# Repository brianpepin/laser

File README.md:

# The Laser Project
This repository contains a design for a diode pumped solid state laser that emits a green 532nm beam.  The unit is battery operated and rechargable with a runtime of approximately 30 minutes.

## Versions
Version 2.1 of the hardware and software is now live. Here is a summary of the changes:
1. The control board now uses a more modern MCU. Display refreshes are 8x faster and I was able to remove a number of components from the board due to the enhanced peripheral support on the new MCU.
2. Encoders are now velocity sensitive.
3. Calibration for the output power monitor now can be done through the UI.
4. The laser design has changed and the maximum output power is now 3x what it was in version 1.

## Repository Organization

The repository contains the following directories.

### Hardware
The Hardware directory contains KiCad files for schematics and board designs for the electronics.  There are three boards in total:

1. The **Power** board is the main power supply. It contains a battery charger, power control, power monitoring, fan controller, and two 50A constant current power supplies.

2. The **TEC** board contains four independent channels for controlling thermo-electric coolers. Each channel can control up to 20A of cooling using direct battery voltage.

3. The **Control** board is a small MCU and display for running the laser.  The board is based on the aging ATMEGA328p....but it would be easy to swap this to a newer MCU.

**Update:** Version 2.1 of the hardware now uses AVR128DB64 as it's MCU. This MCU has a lot more memory, a much faster speed, and perhipherial updates (like controllable schmitt triggers on inputs) that greatly simplified the rest of the board.

The power and TEC boards must both be bonded to heat sinks on the underside of the board using a non-conductive thermal layer. Boards use Deans connectors for high power and these connectors were modified (pins trimmed) so when soldered the back of the board remains relatively flat.

The system is designed to run off a 2S LiPo pack (I'm using two 8Ah packs in parallel). If you need higher voltage for the TECs you can go to 3S but may need to modify the charging circuit, which is designed for a 2S cell.

### Software
The software directory contains the source code for the controller. It uses Platform.IO in Visual Studio Code and levages Arduino libraries for convenience, especially for driving the display. Installing Platform.IO should be sufficient to find dependent libraries.
The software is organized to have a lib directory that contains generic driver code for chips used on each of the boards.  In the src directory these generic classes are wrapped by higher level classes that abstract their use.  For example, lib has directories called ADC104S021 and DAC108S085 for controlling ADC and DAC chips, and src has a class called TEC that uses both these lower level classes but provides an interface in degrees C.

### Optics
Optics contains files relevant to the optical layout.  Files ending in .rez are Rezonator files, which is an open-source program available at http://www.rezonator.orion-project.org which can do ABCD matrix analysis of laser cavities for stability and Gaussian beam analysis.

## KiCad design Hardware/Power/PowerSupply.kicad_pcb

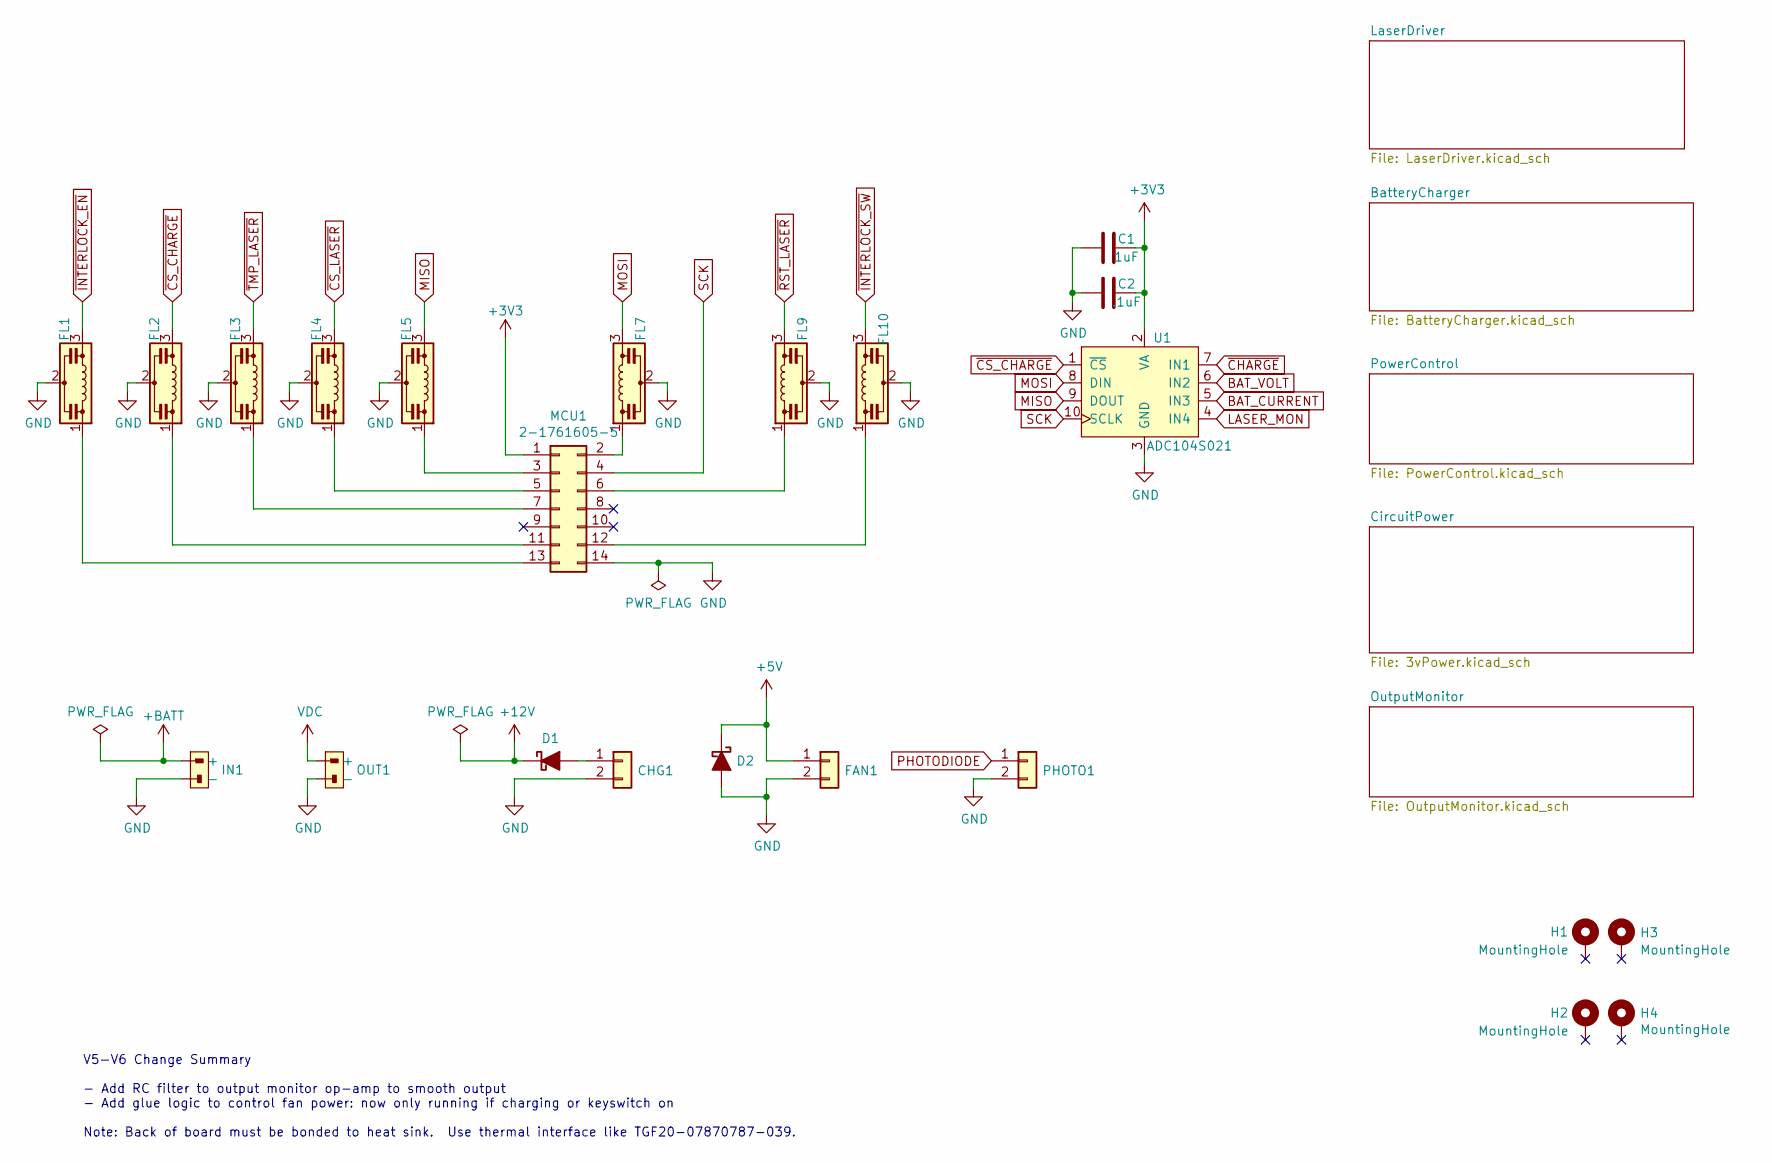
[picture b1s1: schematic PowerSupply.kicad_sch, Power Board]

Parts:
C1: 1uF; C_0805_2012Metric; PartNo UMF212B7105KGHT
C2: .1uF; C_0805_2012Metric; PartNo C0805X104M5RACTU
CHG1: 105313-1102; Molex_Nano-Fit_105313-xx02_1x02_P2.50mm_Horizontal; PartNo 105313-1102
D1: CDBA540-HF; D_SMA; PartNo CDBA540-HF
D2: V1FM15-M3/H; D_SOD-123F; PartNo V1FM15-M3/H
FAN1: 53398-0267; 533980267; PartNo 53398-0267
FL1, FL2, FL3, FL4, FL5, FL7, FL9, FL10: NFL21SP206X1C7D; EMI_805; PartNo NFL21SP206X1C7D
H1, H2, H3, H4: MountingHole; MountingHole_3.2mm_M3_Pad_Via
IN1: DEANS; Connector_Deans_Male
MCU1: 2-1761605-5; IDC-Header_2x07_P2.54mm_Horizontal; PartNo 2-1761605-5
OUT1: DEANS; Connector_Deans_Female
PHOTO1: 53398-0267; 533980267; PartNo 53398-0267
U1: ADC104S021; VSSOP-10_3x3mm_P0.5mm; PartNo ADC104S021CIMMX/NOPB

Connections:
+3V3: C1.1, C2.1, MCU1.1, U1.2 (VA); also elsewhere on the board
+5V: D2.1 (K), FAN1.1; also elsewhere on the board
+12V: D1.1 (K); also elsewhere on the board
+BATT: IN1.+; also elsewhere on the board
BAT_CURRENT: U1.5 (IN3); also elsewhere on the board
BAT_VOLT: U1.6 (IN2); also elsewhere on the board
GND: C1.2, C2.2, CHG1.2, D2.2 (A), FAN1.2, FL1.2, FL2.2, FL3.2, FL4.2, FL5.2, FL7.2, FL9.2, FL10.2, IN1.-, MCU1.14, OUT1.-, PHOTO1.2, U1.3 (GND); also elsewhere on the board
LASER_MON: U1.4 (IN4); also elsewhere on the board
MISO: FL5.3, U1.9 (DOUT); also elsewhere on the board
MOSI: FL7.3, U1.8 (DIN); also elsewhere on the board
unnamed: CHG1.1, D1.2 (A)
unnamed: FL7.1, MCU1.2
unnamed: FL5.1, MCU1.3
unnamed: FL4.1, MCU1.5
unnamed: FL9.1, MCU1.6
unnamed: FL3.1, MCU1.7
unnamed: FL2.1, MCU1.11
unnamed: FL10.1, MCU1.12
unnamed: FL1.1, MCU1.13
PHOTODIODE: PHOTO1.1; also elsewhere on the board
SCK: MCU1.4, U1.10 (SCLK); also elsewhere on the board
VDC: OUT1.+; also elsewhere on the board
~CHARGE: U1.7 (IN1); also elsewhere on the board
~CS_CHARGE: FL2.3, U1.1 (~CS)
~CS_LASER: FL4.3; also elsewhere on the board
~INTERLOCK_EN: FL1.3; also elsewhere on the board
~INTERLOCK_SW: FL10.3; also elsewhere on the board
~RST_LASER: FL9.3; also elsewhere on the board
~TMP_LASER: FL3.3; also elsewhere on the board

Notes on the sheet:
V5-V6 Change Summary - Add RC filter to output monitor op-amp to smooth output - Add glue logic to control fan power: now only running if charging or keyswitch on Note: Back of board must be bonded to heat sink. Use thermal interface like TGF20-07870787-039.

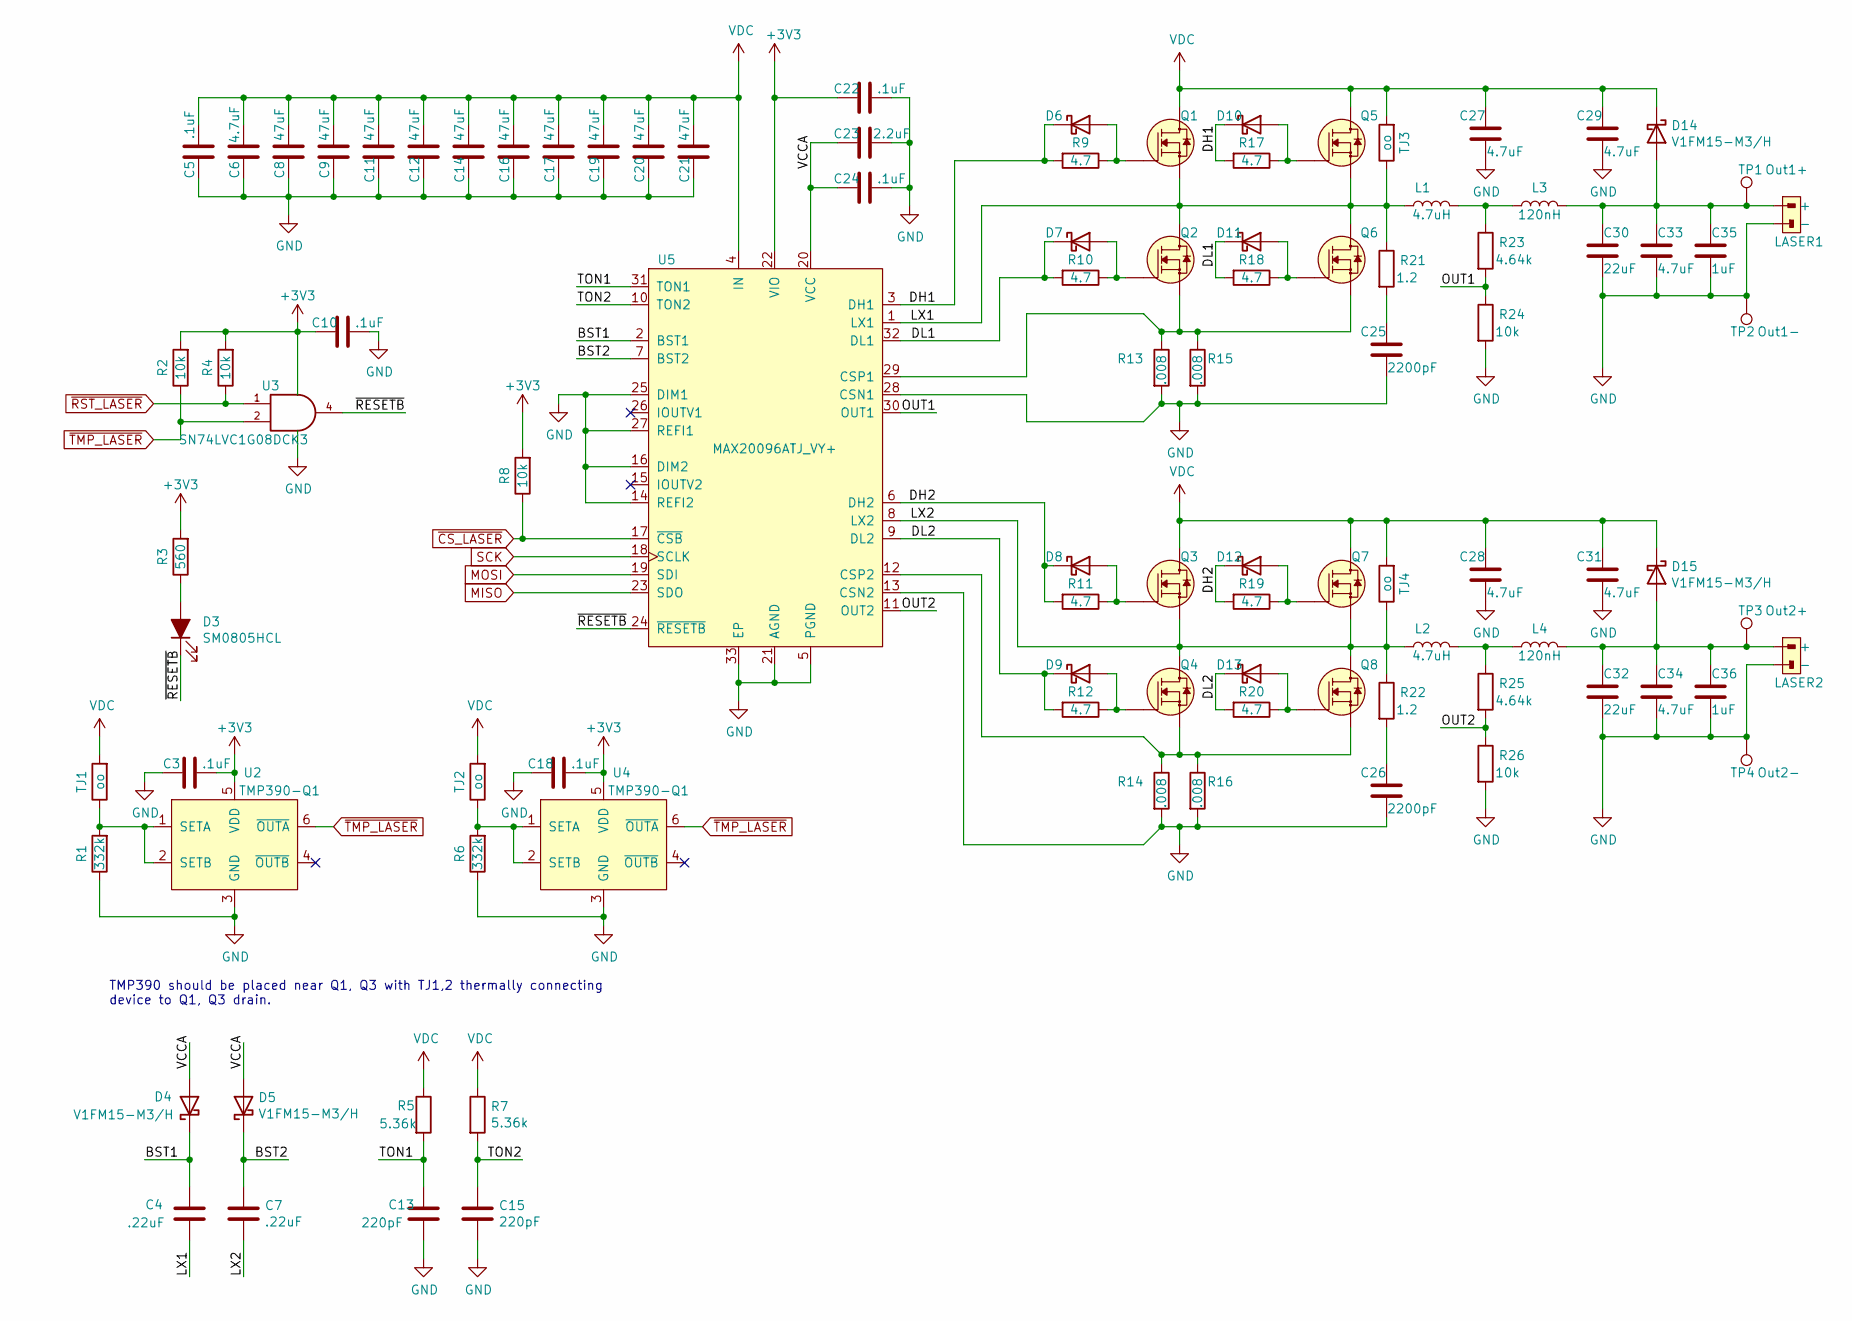
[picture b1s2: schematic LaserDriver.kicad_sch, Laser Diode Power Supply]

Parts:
C3, C5, C10, C18, C22, C24: .1uF; C_0805_2012Metric; PartNo C0805X104M5RACTU
C4, C7: .22uF; C_0805_2012Metric; PartNo GRM21AR72A224KAC5K
C6, C27, C28, C29, C31, C33, C34: 4.7uF; C_0805_2012Metric; PartNo JMK212B7475KGHT
C8, C9, C11, C12, C14, C16, C17, C19, C20, C21: 47uF; C_1206_3216Metric; PartNo C3216JB1E476M160AC
C13, C15: 220pF; C_0805_2012Metric; PartNo C0805C221K1HACTU
C23: 2.2uF; C_0805_2012Metric; PartNo GCM21BR71E225KA73L
C25, C26: 2200pF; C_0805_2012Metric; PartNo C0805C222K3GECTU
C30, C32: 22uF; C_1206_3216Metric; PartNo C3216X5R1V226M160AC
C35, C36: 1uF; C_0805_2012Metric; PartNo UMF212B7105KGHT
D3: SM0805HCL; LED_0805_2012Metric; PartNo SM0805HCL
D4, D5, D6, D7, D8, D9, D10, D11, D12, D13, D14, D15: V1FM15-M3/H; D_SOD-123F; PartNo V1FM15-M3/H
L1, L2: 4.7uH; Inductor_Kemet_MPX1D2213; PartNo MPXV1D2213L4R7
L3, L4: 120nH; Inductor_TDK_VLBS1007083; PartNo VLBU1007090T-R12L
LASER1, LASER2: DEANS; Connector_Deans_Female
Q1, Q2, Q3, Q4, Q5, Q6, Q7, Q8: PSMN1R5-25MLHX; LFPAK33; PartNo PSMN1R5-25MLHX
R1, R6: 332k; R_0805_2012Metric; PartNo RT0805FRE07332KL
R2, R4, R8, R24, R26: 10k; R_0805_2012Metric; PartNo ERJ-6ENF1002V
R3: 560; R_0805_2012Metric; PartNo ERJ-6ENF5600V
R5, R7: 5.36k; R_0805_2012Metric; PartNo ERJ-6ENF5361V
R9, R10, R11, R12, R17, R18, R19, R20: 4.7; R_0805_2012Metric; PartNo ERJ-P06J4R7V
R13, R14, R15, R16: .008; R_2818_7158Metric_Kelvin; PartNo WSHM28188L000FEA
R21, R22: 1.2; R_0805_2012Metric; PartNo ERJ-6BQF1R2V
R23, R25: 4.64k; R_0805_2012Metric; PartNo ERJ-6ENF4641V
TJ1, TJ2, TJ3, TJ4: oo; R_1206_3216Metric; PartNo THJP1206AST1
TP1: Out1+; TestPoint_THTPad_1.0x1.0mm_Drill0.5mm
TP2: Out1-; TestPoint_THTPad_1.0x1.0mm_Drill0.5mm
TP3: Out2+; TestPoint_THTPad_1.0x1.0mm_Drill0.5mm
TP4: Out2-; TestPoint_THTPad_1.0x1.0mm_Drill0.5mm
U2, U4: TMP390-Q1; SOT-563; PartNo TMP390AQDRLRQ1
U3: SN74LVC1G08DCK3; SC-70-5; PartNo SN74LVC1G08DCK3
U5: MAX20096ATJ_VY+; QFN-32-1EP_5x5mm_P0.5mm_EP3.1x3.1mm_ThermalVias; PartNo MAX20096ATJ/VY+

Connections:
+3V3: C3.1, C10.2, C18.1, C22.2, R2.2, R3.2, R4.2, R8.2, U2.5 (VDD), U3.5 (VCC), U4.5 (VDD), U5.22 (VIO); also elsewhere on the board
/LaserDriver/BST1: C4.1, D4.1 (K), U5.2 (BST1)
/LaserDriver/BST2: C7.1, D5.1 (K), U5.7 (BST2)
/LaserDriver/DH1: D6.1 (K), D10.1 (K), R9.2, R17.2, U5.3 (DH1)
/LaserDriver/DH2: D8.1 (K), D12.1 (K), R11.2, R19.2, U5.6 (DH2)
/LaserDriver/DL1: D7.1 (K), D11.1 (K), R10.2, R18.2, U5.32 (DL1)
/LaserDriver/DL2: D9.1 (K), D13.1 (K), R12.2, R20.2, U5.9 (DL2)
/LaserDriver/LX1: C4.2, L1.1, Q1.1 (S), Q1.2 (S), Q1.3 (S), Q2.5 (D), Q5.1 (S), Q5.2 (S), Q5.3 (S), Q6.5 (D), R21.1, TJ3.1, U5.1 (LX1)
/LaserDriver/LX2: C7.2, L2.1, Q3.1 (S), Q3.2 (S), Q3.3 (S), Q4.5 (D), Q7.1 (S), Q7.2 (S), Q7.3 (S), Q8.5 (D), R22.1, TJ4.1, U5.8 (LX2)
/LaserDriver/OUT1: R23.2, R24.1, U5.30 (OUT1)
/LaserDriver/OUT2: R25.2, R26.1, U5.11 (OUT2)
/LaserDriver/TON1: C13.1, R5.2, U5.31 (TON1)
/LaserDriver/TON2: C15.1, R7.2, U5.10 (TON2)
/LaserDriver/VCCA: C23.2, C24.2, D4.2 (A), D5.2 (A), U5.20 (VCC)
/LaserDriver/~RESETB: D3.1 (K), U3.4, U5.24 (~RESETB)
GND: C3.2, C5.2, C6.2, C8.2, C9.2, C10.1, C11.2, C12.2, C13.2, C14.2, C15.2, C16.2, C17.2, C18.2, C19.2, C20.2, C21.2, C22.1, C23.1, C24.1, C25.2, C26.2, C27.2, C28.2, C29.2, C30.2, C31.2, C32.2, C33.2, C34.2, C35.2, C36.2, LASER1.-, LASER2.-, R1.1, R6.1, R13.2, R14.2, R15.2, R16.2, R24.2, R26.2, TP2.1, TP4.1, U2.3 (GND), U3.3 (GND), U4.3 (GND), U5.5 (PGND), U5.13 (CSN2), U5.14 (REFI2), U5.16 (DIM2), U5.21 (AGND), U5.25 (DIM1), U5.27 (REFI1), U5.28 (CSN1), U5.33 (EP); also elsewhere on the board
MISO: U5.23 (SDO); also elsewhere on the board
MOSI: U5.19 (SDI); also elsewhere on the board
unnamed: C25.1, R21.2
unnamed: C26.1, R22.2
unnamed: D3.2 (A), R3.1
unnamed: D6.2 (A), Q1.4 (G), R9.1
unnamed: D7.2 (A), Q2.4 (G), R10.1
unnamed: D8.2 (A), Q3.4 (G), R11.1
unnamed: D9.2 (A), Q4.4 (G), R12.1
unnamed: D10.2 (A), Q5.4 (G), R17.1
unnamed: D11.2 (A), Q6.4 (G), R18.1
unnamed: D12.2 (A), Q7.4 (G), R19.1
unnamed: D13.2 (A), Q8.4 (G), R20.1
unnamed: C30.1, C33.1, C35.1, D14.2 (A), L3.2, LASER1.+, TP1.1
unnamed: C32.1, C34.1, C36.1, D15.2 (A), L4.2, LASER2.+, TP3.1
unnamed: L1.2, L3.1, R23.1
unnamed: L2.2, L4.1, R25.1
unnamed: R1.2, TJ1.1, U2.1 (SETA), U2.2 (SETB)
unnamed: R6.2, TJ2.1, U4.1 (SETA), U4.2 (SETB)
unnamed: Q2.1 (S), Q2.2 (S), Q2.3 (S), Q6.1 (S), Q6.2 (S), Q6.3 (S), R13.1, R15.1, U5.29 (CSP1)
unnamed: Q4.1 (S), Q4.2 (S), Q4.3 (S), Q8.1 (S), Q8.2 (S), Q8.3 (S), R14.1, R16.1, U5.12 (CSP2)
SCK: U5.18 (SCLK); also elsewhere on the board
VDC: C5.1, C6.1, C8.1, C9.1, C11.1, C12.1, C14.1, C16.1, C17.1, C19.1, C20.1, C21.1, C27.1, C28.1, C29.1, C31.1, D14.1 (K), D15.1 (K), Q1.5 (D), Q3.5 (D), Q5.5 (D), Q7.5 (D), R5.1, R7.1, TJ1.2, TJ2.2, TJ3.2, TJ4.2, U5.4 (IN); also elsewhere on the board
~CS_LASER: R8.1, U5.17 (~CSB); also elsewhere on the board
~RST_LASER: R4.1, U3.1; also elsewhere on the board
~TMP_LASER: R2.1, U2.6 (~OUTA), U3.2, U4.6 (~OUTA); also elsewhere on the board

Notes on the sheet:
TMP390 should be placed near Q1, Q3 with TJ1,2 thermally connecting device to Q1, Q3 drain.

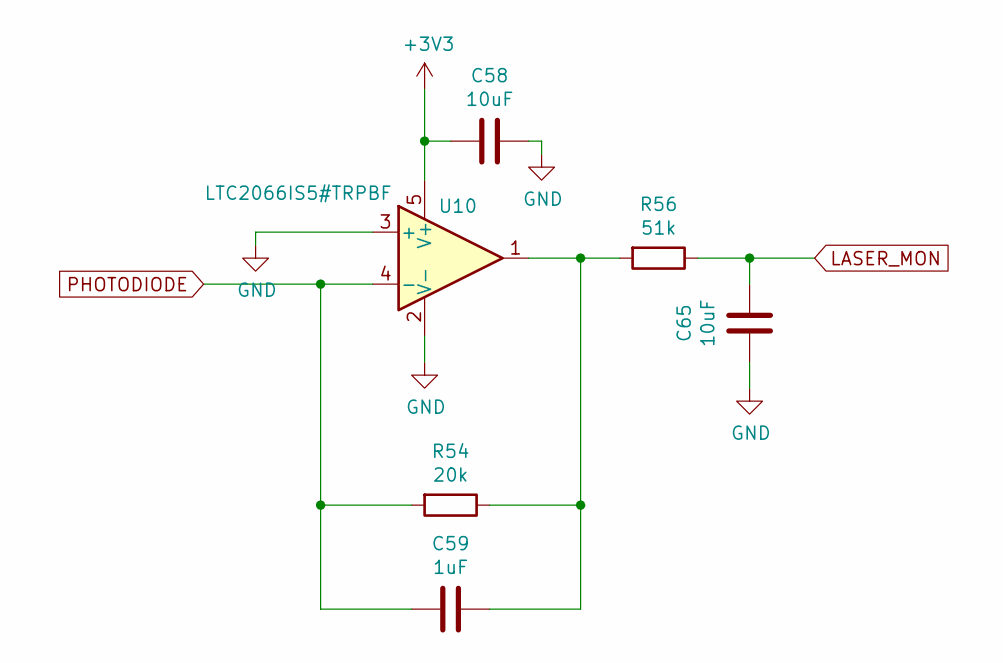
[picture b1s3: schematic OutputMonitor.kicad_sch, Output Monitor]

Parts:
C58, C65: 10uF; C_0805_2012Metric; PartNo C0805X104M5RACTU
C59: 1uF; C_0805_2012Metric; PartNo UMF212B7105KGHT
R54: 20k; R_0805_2012Metric; PartNo ERJ-P06D60R4V
R56: 51k; R_0805_2012Metric; PartNo ERJ-P06D60R4V
U10: LTC2066IS5#TRPBF; SOT-23-5; PartNo LTC2066IS5#TRPBF

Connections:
+3V3: C58.2, U10.5 (V+); also elsewhere on the board
GND: C58.1, C65.2, U10.2 (V-), U10.3 (+); also elsewhere on the board
LASER_MON: C65.1, R56.1; also elsewhere on the board
unnamed: C59.1, R54.1, R56.2, U10.1
PHOTODIODE: C59.2, R54.2, U10.4 (-); also elsewhere on the board

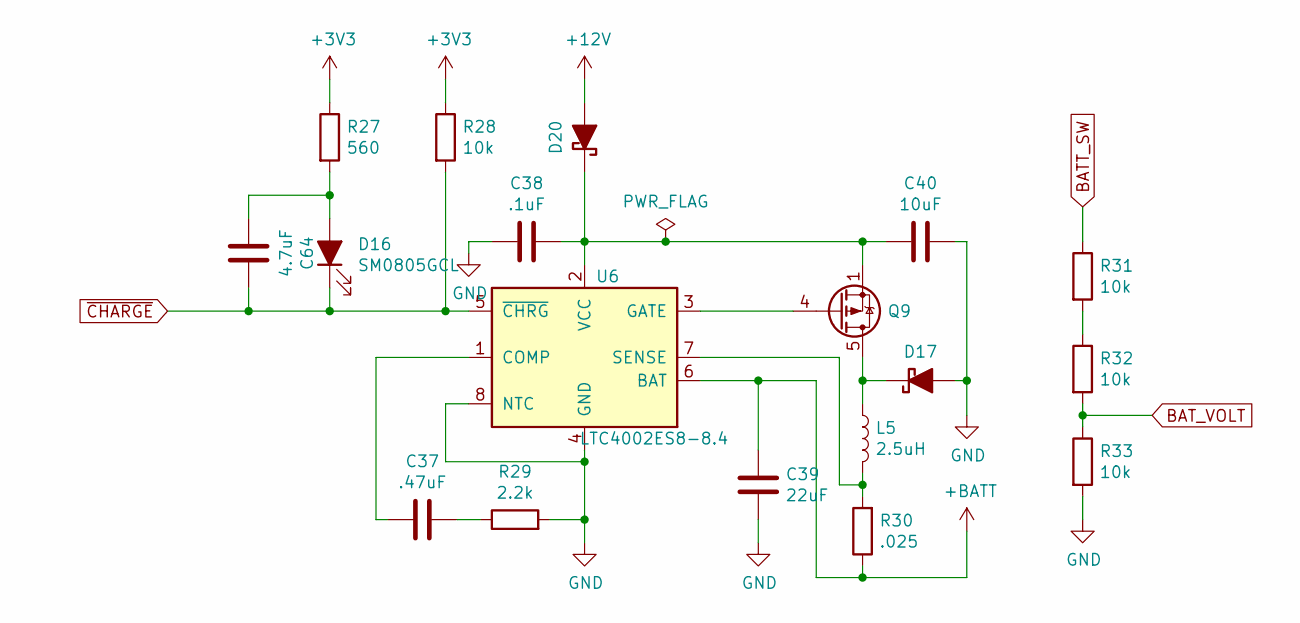
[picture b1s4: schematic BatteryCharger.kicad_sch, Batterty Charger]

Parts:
C37: .47uF; C_0805_2012Metric; PartNo C2012X7R1E474K125AA
C38: .1uF; C_0805_2012Metric; PartNo C0805X104M5RACTU
C39: 22uF; C_1206_3216Metric; PartNo C3216X5R1V226M160AC
C40: 10uF; C_1206_3216Metric; PartNo GMK316AB7106KL-TR
C64: 4.7uF; C_0805_2012Metric; PartNo JMK212B7475KGHT
D16: SM0805GCL; LED_0805_2012Metric; PartNo SM0805GCL
D17, D20: CDBA540-HF; D_SMA; PartNo CDBA540-HF
L5: 2.5uH; Inductor_Pulse_PA4341; PartNo PA4341.252NLT
Q9: Si7141DP; PowerPAK_SO-8_Single; PartNo SI7141DP-T1-GE3
R27: 560; R_0805_2012Metric; PartNo ERJ-6ENF5600V
R28, R31, R32, R33: 10k; R_0805_2012Metric; PartNo ERJ-6ENF1002V
R29: 2.2k; R_0805_2012Metric; PartNo ERJ-PB6B2201V
R30: .025; R_2010_5025Metric; PartNo WSL2010R0250FEA
U6: LTC4002ES8-8.4; SOIC-8_3.9x4.9mm_P1.27mm; PartNo LTC4002ES8-8.4#PBF

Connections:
+3V3: R27.1, R28.1; also elsewhere on the board
+12V: D20.2 (A); also elsewhere on the board
+BATT: C39.1, R30.1, U6.6 (BAT); also elsewhere on the board
BATT_SW: R31.1; also elsewhere on the board
BAT_VOLT: R32.2, R33.1; also elsewhere on the board
GND: C38.2, C39.2, C40.1, D17.2 (A), R29.2, R33.2, U6.4 (GND), U6.8 (NTC); also elsewhere on the board
unnamed: C37.1, R29.1
unnamed: C64.2, D16.2 (A), R27.2
unnamed: D17.1 (K), L5.1, Q9.5 (D)
unnamed: C38.1, C40.2, D20.1 (K), Q9.1 (S), Q9.2 (S), Q9.3 (S), U6.2 (VCC)
unnamed: Q9.4 (G), U6.3 (GATE)
unnamed: R31.2, R32.1
unnamed: C37.2, U6.1 (COMP)
unnamed: L5.2, R30.2, U6.7 (SENSE)
~CHARGE: C64.1, D16.1 (K), R28.2, U6.5 (~CHRG); also elsewhere on the board

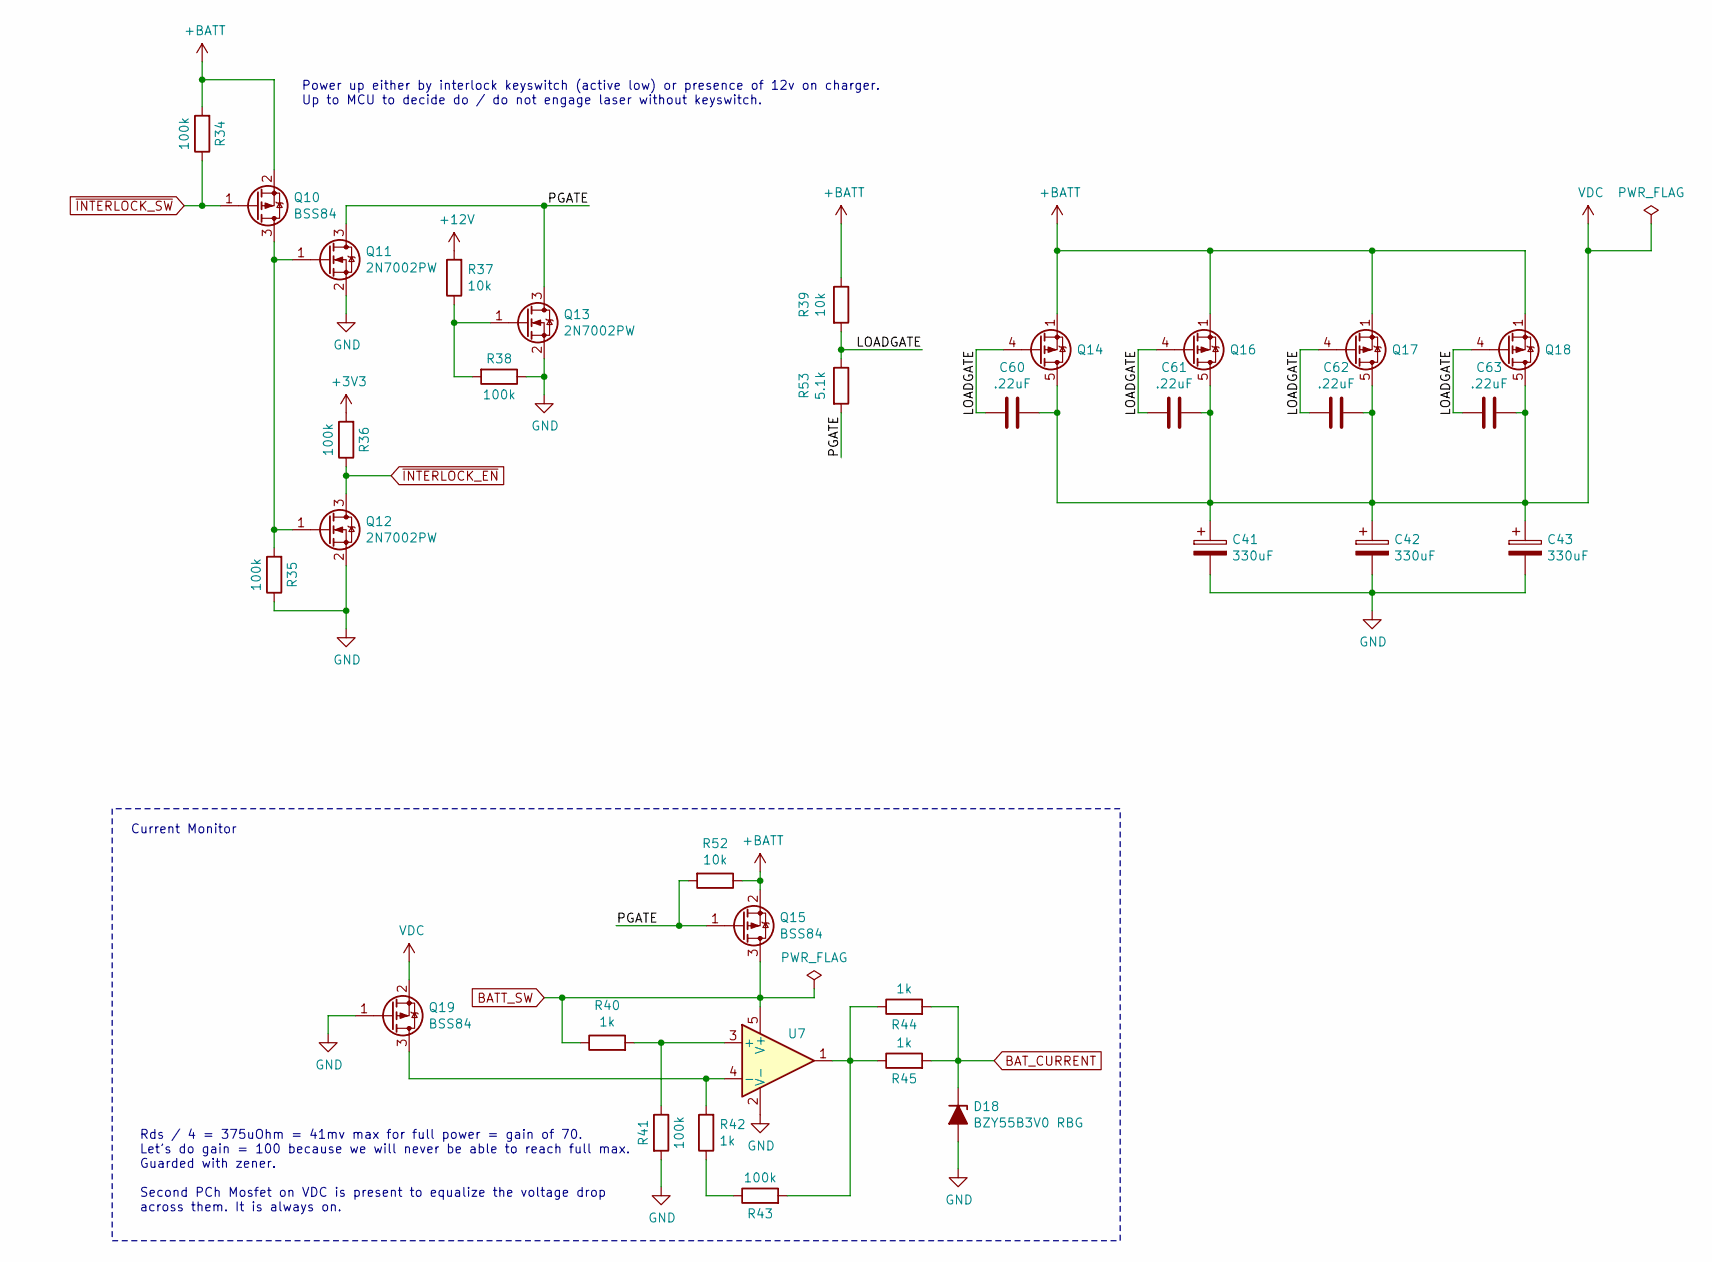
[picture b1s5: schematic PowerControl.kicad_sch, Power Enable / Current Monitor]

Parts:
C41, C42, C43: 330uF; CP_Elec_10x10; PartNo GYC1E331MCQ1GS
C60, C61, C62, C63: .22uF; C_0603_1608Metric
D18: BZY55B3V0 RBG; D_0805_2012Metric; PartNo BZY55B3V0 RBG
Q10, Q15, Q19: BSS84; SOT-323_SC-70; PartNo BSS84PWH6327XT
Q11, Q12, Q13: 2N7002PW; SOT-323_SC-70; PartNo 2N7002PW,115
Q14, Q16, Q17, Q18: Si7141DP; PowerPAK_SO-8_Single; PartNo SI7141DP-T1-GE3
R34, R35, R36, R38, R41, R43: 100k; R_0805_2012Metric; PartNo SFR10EZPJ104
R37, R39, R52: 10k; R_0805_2012Metric; PartNo ERJ-6ENF1002V
R40, R42, R44, R45: 1k; R_0805_2012Metric; PartNo ERJ-P06J102V
R53: 5.1k; R_0805_2012Metric
U7: LTC2066IS5#TRPBF; SOT-23-5; PartNo LTC2066IS5#TRPBF

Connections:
+3V3: R36.2; also elsewhere on the board
+12V: R37.2; also elsewhere on the board
+BATT: Q10.2 (S), Q14.1 (S), Q14.2 (S), Q14.3 (S), Q15.2 (S), Q16.1 (S), Q16.2 (S), Q16.3 (S), Q17.1 (S), Q17.2 (S), Q17.3 (S), Q18.1 (S), Q18.2 (S), Q18.3 (S), R34.2, R39.1, R52.1; also elsewhere on the board
/PowerControl/LOADGATE: C60.2, C61.2, C62.2, C63.2, Q14.4 (G), Q16.4 (G), Q17.4 (G), Q18.4 (G), R39.2, R53.1
/PowerControl/PGATE: Q11.3 (D), Q13.3 (D), Q15.1 (G), R52.2, R53.2
BATT_SW: Q15.3 (D), R40.1, U7.5 (V+); also elsewhere on the board
BAT_CURRENT: D18.1 (K), R44.2, R45.2; also elsewhere on the board
GND: C41.2, C42.2, C43.2, D18.2 (A), Q11.2 (S), Q12.2 (S), Q13.2 (S), Q19.1 (G), R35.1, R38.1, R41.2, U7.2 (V-); also elsewhere on the board
unnamed: Q10.3 (D), Q11.1 (G), Q12.1 (G), R35.2
unnamed: Q13.1 (G), R37.1, R38.2
unnamed: Q19.3 (D), R42.2, U7.4 (-)
unnamed: R42.1, R43.1
unnamed: R43.2, R44.1, R45.1, U7.1
unnamed: R40.2, R41.1, U7.3 (+)
VDC: C41.1, C42.1, C43.1, C60.1, C61.1, C62.1, C63.1, Q14.5 (D), Q16.5 (D), Q17.5 (D), Q18.5 (D), Q19.2 (S); also elsewhere on the board
~INTERLOCK_EN: Q12.3 (D), R36.1; also elsewhere on the board
~INTERLOCK_SW: Q10.1 (G), R34.1; also elsewhere on the board

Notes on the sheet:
Power up either by interlock keyswitch (active low) or presence of 12v on charger. Up to MCU to decide do / do not engage laser without keyswitch.
Current Monitor
Rds / 4 = 375uOhm = 41mv max for full power = gain of 70. Let’s do gain = 100 because we will never be able to reach full max. Guarded with zener. Second PCh Mosfet on VDC is present to equalize the voltage drop across them. It is always on.

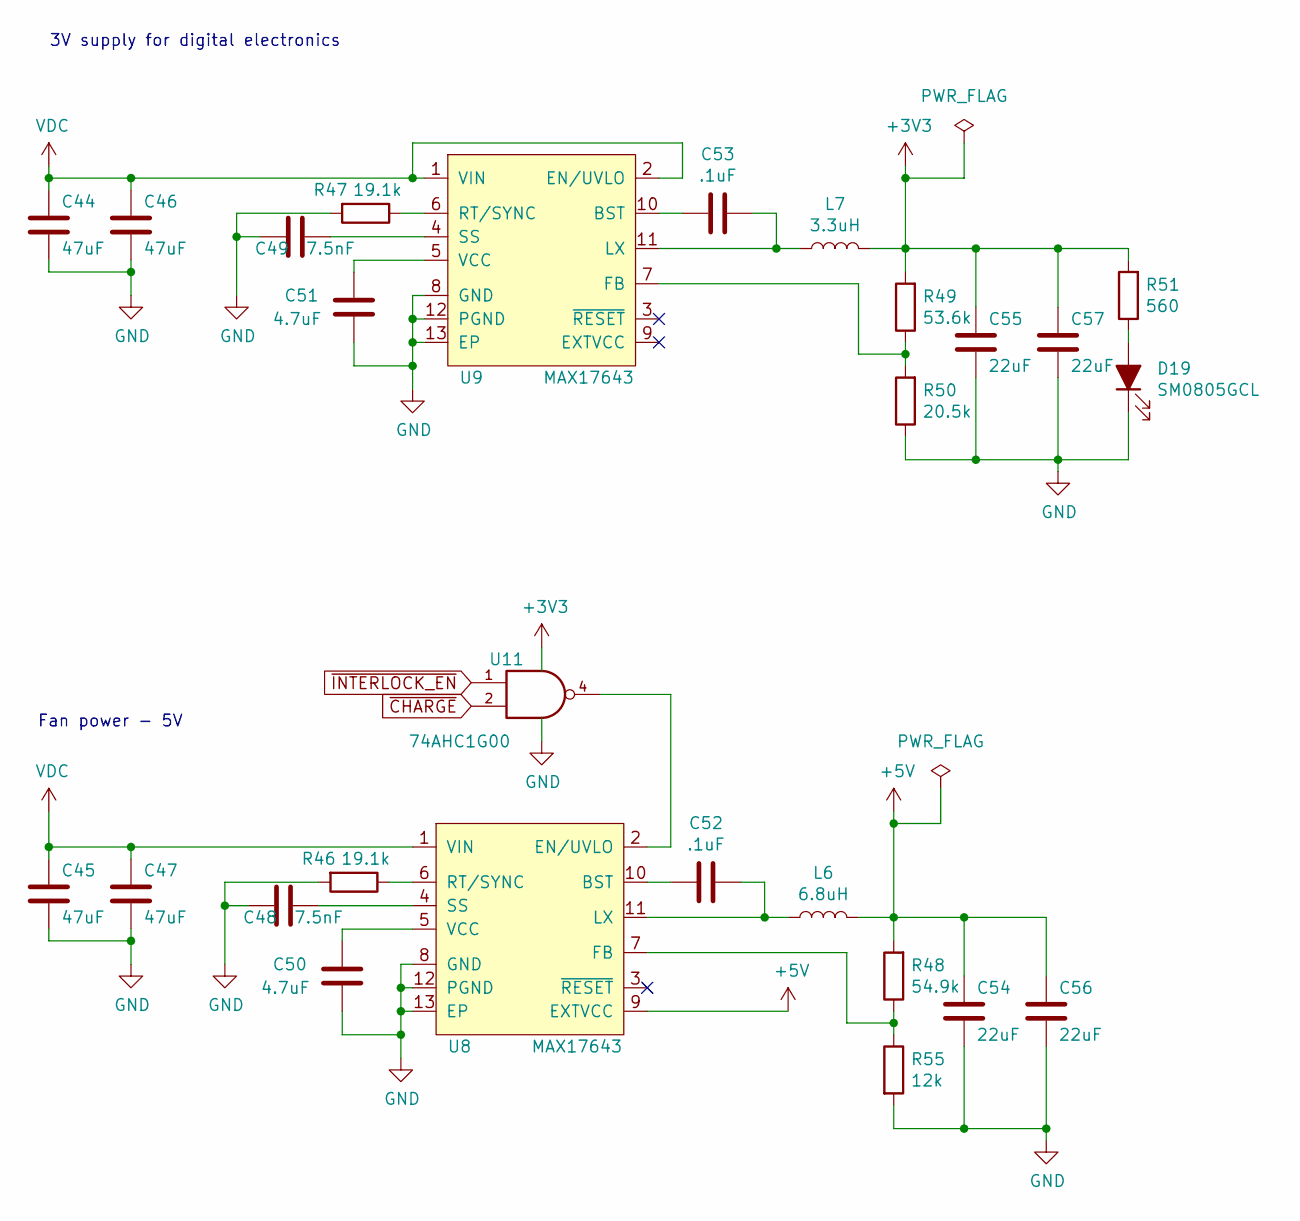
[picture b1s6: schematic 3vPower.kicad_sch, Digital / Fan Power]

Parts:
C44, C45, C46, C47: 47uF; C_1206_3216Metric; PartNo C3216JB1E476M160AC
C48, C49: 7.5nF; C_0805_2012Metric; PartNo C0805C752F8HACTU
C50, C51: 4.7uF; C_0805_2012Metric; PartNo JMK212B7475KGHT
C52, C53: .1uF; C_0805_2012Metric; PartNo C0805X104M5RACTU
C54, C55, C56, C57: 22uF; C_1206_3216Metric; PartNo C3216X5R1V226M160AC
D19: SM0805GCL; LED_0805_2012Metric; PartNo SM0805GCL
L6: 6.8uH; Inductor_SRP0412; PartNo SRP0412-6R8K
L7: 3.3uH; Inductor_SRP0412; PartNo SRP0412-3R3K
R46, R47: 19.1k; R_0805_2012Metric; PartNo ERJ-6ENF1912V
R48: 54.9k; R_0805_2012Metric; PartNo ERJ-6ENF5492V
R49: 53.6k; R_0805_2012Metric; PartNo ERJ-6ENF5362V
R50: 20.5k; R_0805_2012Metric; PartNo ERJ-6ENF2052V
R51: 560; R_0805_2012Metric; PartNo ERJ-6ENF5600V
R55: 12k; R_0805_2012Metric; PartNo ERJ-P06F1202V
U8, U9: MAX17643; DFN-12-1EP_3x3mm_P0.5mm_EP2.05x2.5mm; PartNo MAX17643ATC+
U11: 74AHC1G00; SOT-23-5; PartNo SN74AHC1G00DBVR

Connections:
+3V3: C55.2, C57.2, L7.2, R49.2, R51.2, U11.5 (VCC); also elsewhere on the board
+5V: C54.2, C56.2, L6.2, R48.2, U8.9 (EXTVCC); also elsewhere on the board
GND: C44.1, C45.1, C46.1, C47.1, C48.2, C49.2, C50.1, C51.1, C54.1, C55.1, C56.1, C57.1, D19.1 (K), R46.2, R47.2, R50.1, R55.2, U8.8 (GND), U8.12 (PGND), U8.13 (EP), U9.8 (GND), U9.12 (PGND), U9.13 (EP), U11.3 (GND); also elsewhere on the board
unnamed: D19.2 (A), R51.1
unnamed: C52.2, U8.10 (BST)
unnamed: U8.2 (EN/UVLO), U11.4
unnamed: R48.1, R55.1, U8.7 (FB)
unnamed: C52.1, L6.1, U8.11 (LX)
unnamed: R46.1, U8.6 (RT/SYNC)
unnamed: C48.1, U8.4 (SS)
unnamed: C50.2, U8.5 (VCC)
unnamed: C53.2, U9.10 (BST)
unnamed: R49.1, R50.2, U9.7 (FB)
unnamed: C53.1, L7.1, U9.11 (LX)
unnamed: R47.1, U9.6 (RT/SYNC)
unnamed: C49.1, U9.4 (SS)
unnamed: C51.2, U9.5 (VCC)
VDC: C44.2, C45.2, C46.2, C47.2, U8.1 (VIN), U9.1 (VIN), U9.2 (EN/UVLO); also elsewhere on the board
~CHARGE: U11.2; also elsewhere on the board
~INTERLOCK_EN: U11.1; also elsewhere on the board

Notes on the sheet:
Fan power - 5V
3V supply for digital electronics

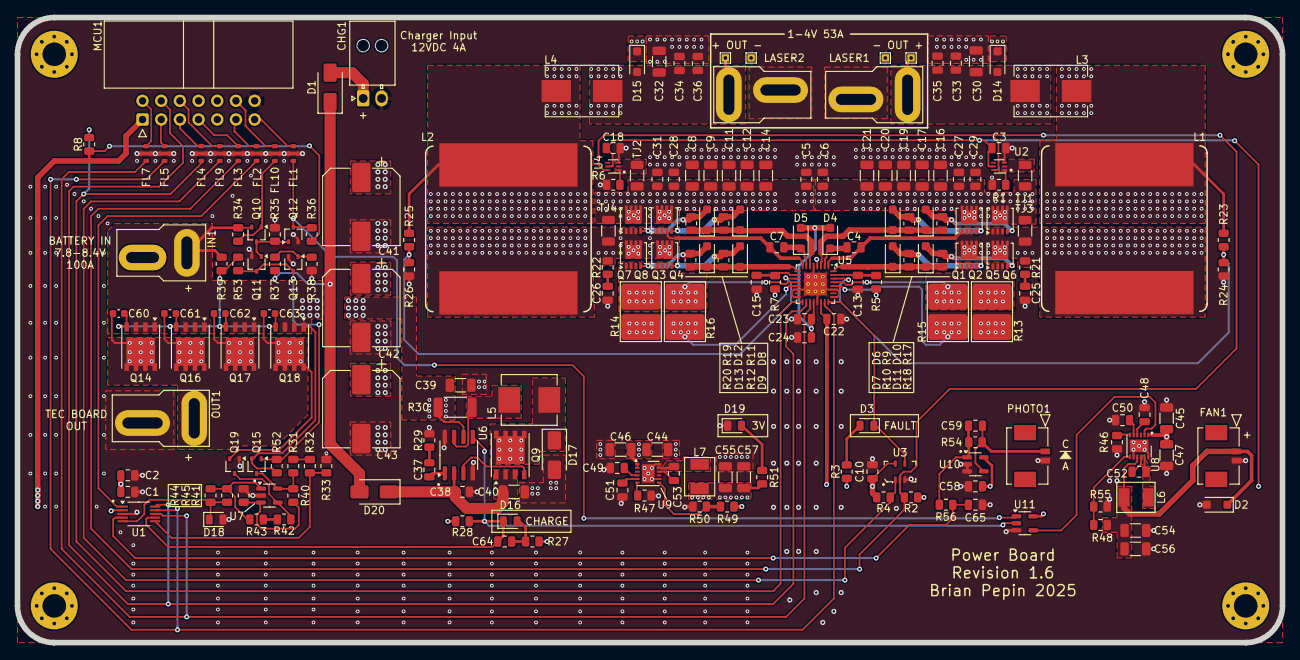
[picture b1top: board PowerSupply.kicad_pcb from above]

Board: 4 copper layers, 172.0 x 85.0 mm, 206 parts (0 on the bottom side), 94 nets.

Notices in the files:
parts and their libraries:
Copyright 2021 Accelerated Designs. All rights reserved.
